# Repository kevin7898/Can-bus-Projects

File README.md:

# CAN bus projects

Experiments and applications built around CAN/OBD vehicle data.

## Projects

### [Jetta Recorder Android](jetta-recorder-android/)

An Android-first, local-first driving recorder for the Volkswagen Jetta, initially targeting a OnePlus 6T and OBDLink MX+.

The first hardware milestone establishes a real ELM327/STN connection, records standard OBD-II telemetry, captures raw CAN observations, and exports evidence for decoder development.

> Privacy: raw captures, GPS traces, VINs, and personal vehicle logs are intentionally excluded from this public repository.

### [CAN / CONNECT iOS companion](can-connect-ios/)

Native SwiftUI iPhone companion using the locked paged CAN / CONNECT design. Open `can-connect-ios/CANConnect.xcodeproj` in Xcode for vehicle onboarding, GPS and Wi-Fi ELM327 recording, fuel logging, import/export and verified transfers to the native Mac server. Hardware acceptance remains outstanding; see the iOS hardware checklist.

### [CAN / CONNECT Mac — locked design](mac-app/design/)

Approved widescreen Mac UI baseline, interactive preview, and native macOS implementation handoff. The design is locked; hardware, import, and server behavior in the preview uses illustrative data.

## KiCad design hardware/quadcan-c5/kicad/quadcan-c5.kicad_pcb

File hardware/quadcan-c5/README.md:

# QuadCAN-C5: 4-channel CAN-FD logger

**Rev 1.1 battery prototype — engineering draft, not released for manufacture.**
See [the revision notes and verification limits](docs/BATTERY_REVISION.md). Firmware for this revision is incompatible with the rev 1.0 pin map.

A custom, from-scratch take on the MrDIY DuoCAN idea, grown into a set-and-forget vehicle logger:

* **4 independent CAN / CAN-FD channels.** The ESP32-C5 has two native CAN-FD controllers, plus 2 × MCP2518FD.
* **One harness connector, swappable vehicle cables:** OBD-II (gateway + power) or heavy-duty
  **J1939** Deutsch 9-pin. Cable-ID pins tell the firmware which cable is attached. See [docs/CABLES.md](docs/CABLES.md).
* **Onboard microSD logging** with a protected 1S Li-ion backup power path and a 30-second crank grace period.
  A **real-time clock** with coin-cell backup timestamps every file.
* **Wi-Fi 6 dual-band + Wi-Fi Aware** (ESP32-C5) for a phone link, plus an optional soft-AP fallback.
* **Optional u-blox NEO-M9N GPS** at 20 Hz (25 Hz max) with an active-antenna u.FL. Leave it
  unpopulated to rely on the phone's location.
* **LTE add-on header** (UART + power key + VIN) for a Cat-1 module board.
* **9–36 V input** for 12 V cars and 24 V trucks.
* **Key-off sleep** (rev 1.1 current not yet measured): wakes on traffic on any of the four buses, an ignition wire, or the
  battery voltage rising when the engine starts. See [docs/LOW_POWER.md](docs/LOW_POWER.md).
* **Bus-safe by construction:** transceivers boot in standby, firmware opens channels listen-only,
  and a channel can't transmit at all unless its **TX_EN** jumper is fitted.

The 140 × 85 mm, four-layer prototype retains four high-speed CAN channels. It does **not** support the Jetta's 100 kbit/s fault-tolerant comfort bus without a different physical-layer design.

```mermaid
flowchart TD
    V["Protected vehicle buck"] --> O["Diode-isolated charger input"]
    U["5 V bench supply via JP9"] --> O
    O --> C["BQ24074 power path"]
    B["Protected 1S pack + NTC"] <--> C
    C --> R["5 V boost with hardware UVLO"]
    R --> T["CAN transceivers"]
    R --> L["3.3 V LDO: processor, SD, GPS"]
```

The LTE header's VIN feed is not battery-backed. JP9 defaults open; USB data remains available. A battery pack and its mounting are external to the PCB BOM.

## Repository layout

| Path | What |
|---|---|
| `gen/design.py` | **Single source of truth**: every part, footprint, MPN and pin-to-net connection |
| `gen/gen_lib.py` | Custom symbols + the ESP32-C5-WROOM-1 footprint (from Espressif's land pattern) |
| `gen/gen_sch.py` | Generates the KiCad schematic from `design.py` |
| `gen/gen_pcb.py` | Board outline, 4-layer stack, placement, ground pours |
| `gen/route.py`, `route_core.c` | Autorouter: direction-aware A* (C core) + rip-up-and-reroute; 45° tracks, In1.Cu kept as solid GND |
| `render/` | Bare-board and 3D renders (`render/render.sh` → `docs/renders/`) |
| `gen/build.sh` | Runs the whole chain: schematic → netlist check → board → route → DRC → fab files |
| `kicad/` | Generated KiCad 9 project (open `quadcan-c5.kicad_pro`) |
| `fab/` | Gerbers (zip), drill, BOM, pick-and-place, schematic PDF, DRC report |
| `firmware/` | ESP-IDF v6 firmware + `.qcl` log converter |
| `enclosure/` | OpenSCAD two-part case + STLs |
| `docs/CABLES.md` | Harness pinout, OBD-II and J1939 cable builds, jumper rules |

## Key design decisions

| Choice | Why |
|---|---|
| ESP32-C5-WROOM-1-N8R8 | Two native CAN-FD controllers, 5 GHz Wi-Fi 6, Wi-Fi Aware support in ESP-IDF, 8 MB PSRAM for a deep log buffer |
| MCP2518FD for CAN3/4 | CAN-FD, 2 KB message RAM (20-frame RX FIFO with hardware timestamps), shares SPI with the SD card |
| TCAN1044AV-Q1 | CAN-FD rated, separate 3.3 V I/O supply, ~15 µA standby with bus wake-up. NXP TJA1044GT/3 is a drop-in alternative. |
| TPS54360 60 V buck | Wide-input converter behind TVS/fuse protection; vehicle transient tolerance requires testing. |
| BQ24074 + protected 1S pack + 5 V boost | Backs the CAN and logic rails through cranking; 30-second firmware grace |
| TCA9535 expander | Frees ESP32 pins; resets to inputs, so every transceiver's STB line floats high (standby) until firmware decides otherwise |
| Molex Micro-Fit 2×7 | Locking, vibration-rated, cheap to crimp; one plug for any vehicle cable |

## Prototype status

The design is not released for ordering. See [fab/STATUS.md](fab/STATUS.md) for measured automated-check results and [docs/BATTERY_REVISION.md](docs/BATTERY_REVISION.md) for unresolved hardware and firmware gates. Fabrication data, if generated, is for engineering review only. BOM passive MPNs, pack selection and assembly rotations still need procurement review.

## Rebuilding

```sh
sudo apt install kicad   # KiCad 9.x
pip install kiutils numpy scipy pillow   # plus gcc for the router core
SKIP_ROUTE=1 bash hardware/quadcan-c5/gen/build.sh
```

The checked route cache is tied to a SHA-256 of the placement geometry. A geometry change invalidates it; omit `SKIP_ROUTE` for a new routing run, then review its new DRC results. The fine-grid finishing pass operates only on signal/ground escapes.

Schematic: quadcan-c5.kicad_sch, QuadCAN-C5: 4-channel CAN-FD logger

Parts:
BT1: CR1220; BatteryHolder_Keystone_3000_1x12mm; MPN Keystone 3000 + CR1220
C1: 47uF 63V; CP_Radial_D8.0mm_P3.50mm; MPN 47uF 63V low-ESR electrolytic, 8mm
C2, C3: 2.2uF 100V; C_1210_3225Metric; MPN 2.2uF 100V 1210 X7R/X5R
C4, C12, C14, C22, C23, C24, C25, C26, C27, C28, C29, C33, C34, C40, C42, C43, C44, C46, C47, C96, C98, C99, C100, C101, C102, C103: 100nF; C_0603_1608Metric; MPN 100nF 0603 X7R/X5R
C5, C6: 47uF 10V; C_1210_3225Metric; MPN 47uF 10V 1210 X7R/X5R
C7: 6.8nF; C_0603_1608Metric; MPN 6.8nF 0603 X7R/X5R
C8: 39pF; C_0603_1608Metric; MPN 39pF 0603 C0G
C10, C45: 10uF; C_0805_2012Metric; MPN 10uF 0805 X7R/X5R
C11, C13: 22uF; C_0805_2012Metric; MPN 22uF 0805 X7R/X5R
C15: 1uF; C_0603_1608Metric; MPN 1uF 0603 X7R/X5R
C41: 4.7uF; C_0805_2012Metric; MPN 4.7uF 0805 X7R/X5R
C90: 4.7uF 10V; C_0805_2012Metric; MPN 4.7uF 10V 0805 X7R/X5R
C91, C93: 10uF 10V; C_0805_2012Metric; MPN 10uF 10V 0805 X7R/X5R
C92, C94, C95: 22uF 10V; C_1210_3225Metric; MPN 22uF 10V 1210 X7R/X5R
C97: 1nF; C_0603_1608Metric; MPN 1nF 0603 X7R/X5R
D1: SMBJ36A; D_SMB; MPN SMBJ36A 600W TVS (36V standoff)
D2, D3: B360A; D_SMA; MPN Diodes B360A-13-F 60V 3A
D4, D5: B5819W; D_SOD-123; MPN B5819W 40V 1A
D11, D12, D13, D14: NUP2105L; SOT-23; MPN onsemi NUP2105LT1G
D21, D22, D23, D24: RX yellow; LED_0603_1608Metric; MPN 0603 LED RX yellow
D30: green; LED_0603_1608Metric; MPN 0603 LED green
D31, D32: blue; LED_0603_1608Metric; MPN 0603 LED blue
D33: GPS green; LED_0603_1608Metric; MPN 0603 LED GPS green
D40, D41: BAT54A; SOT-23; MPN BAT54A dual Schottky, common anode
F1: 2A; Fuse_Littelfuse-NANO2-451_453; MPN Littelfuse 0453002.MR (Nano2 2A 125V)
F2: 1.5A; Fuse_Littelfuse-NANO2-451_453; MPN Littelfuse 045301.5MR
H1, H2, H3, H4: M3; MountingHole_3.2mm_M3
J1: HARNESS; Molex_Micro-Fit_3.0_43045-1400_2x07_P3.00mm_Horizontal; MPN Molex 43045-1400 (mates 43025-1400 + 43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
J2: USB-C; USB_C_Receptacle_HRO_TYPE-C-31-M-12; MPN HRO TYPE-C-31-M-12
J3: microSD; microSD_HC_Hirose_DM3AT-SF-PEJM5; MPN Hirose DM3AT-SF-PEJM5
J4: GPS ANT; U.FL_Hirose_U.FL-R-SMT-1_Vertical; MPN Hirose U.FL-R-SMT-1(10) - active antenna
J5: LTE; PinHeader_1x08_P2.54mm_Vertical; MPN 1x8 2.54mm header
J6: QWIIC; JST_SH_SM04B-SRSS-TB_1x04-1MP_P1.00mm_Horizontal; MPN JST SM04B-SRSS-TB
J7: BATTERY; JST_PH_B3B-PH-K_1x03_P2.00mm_Vertical; MPN JST B3B-PH-K-S
JP1: TERM1; PinHeader_1x02_P2.54mm_Vertical; MPN 1x2 2.54mm header + jumper cap
JP2: TERM2; PinHeader_1x02_P2.54mm_Vertical; MPN 1x2 2.54mm header + jumper cap
JP3: TERM3; PinHeader_1x02_P2.54mm_Vertical; MPN 1x2 2.54mm header + jumper cap
JP4: TERM4; PinHeader_1x02_P2.54mm_Vertical; MPN 1x2 2.54mm header + jumper cap
JP5: TX_EN1; PinHeader_1x02_P2.54mm_Vertical; MPN 1x2 2.54mm header + jumper cap
JP6: TX_EN2; PinHeader_1x02_P2.54mm_Vertical; MPN 1x2 2.54mm header + jumper cap
JP7: TX_EN3; PinHeader_1x02_P2.54mm_Vertical; MPN 1x2 2.54mm header + jumper cap
JP8: TX_EN4; PinHeader_1x02_P2.54mm_Vertical; MPN 1x2 2.54mm header + jumper cap
JP9: USB_POWER; PinHeader_1x02_P2.54mm_Vertical; MPN 2.54mm jumper, default OPEN
L1: 8.2uH; L_Bourns_SRP7028A_7.3x6.6mm; MPN Bourns SRP7028A-8R2M
L2: 27nH; L_0603_1608Metric; MPN Murata LQW18AN27NG00 (27nH)
L3: 1uH; L_Bourns_SRP7028A_7.3x6.6mm; MPN Bourns SRP7028A-1R0M
Q1: MMBT3904; SOT-23; MPN MMBT3904
Q2, Q3: AO3401A; SOT-23; MPN AOS AO3401A P-MOSFET
R1: 523k; R_0603_1608Metric; MPN 523k 0603 1%
R2: 84.5k; R_0603_1608Metric; MPN 84.5k 0603 1%
R3: 162k; R_0603_1608Metric; MPN 162k 0603 1%
R4: 13.0k; R_0603_1608Metric; MPN 13.0k 0603 1%
R5: 53.6k; R_0603_1608Metric; MPN 53.6k 0603 1%
R6: 10.2k; R_0603_1608Metric; MPN 10.2k 0603 1%
R8, R14, R16, R63, R96, R99: 1M; R_0603_1608Metric; MPN 1M 0603 1%
R9, R10, R12, R64, R65, R66, R67, R73, R80, R92, R93, R95, R100, R102: 100k; R_0603_1608Metric; MPN 100k 0603 1%
R11, R17, R20, R21, R22, R53, R55, R60, R61, R62, R104, R105: 10k; R_0603_1608Metric; MPN 10k 0603 1%
R13, R15, R41, R42, R43, R44, R70, R71, R72, R81, R82, R84: 1k; R_0603_1608Metric; MPN 1k 0603 1%
R18, R19: 4.7k; R_0603_1608Metric; MPN 4.7k 0603 1%
R23, R24: 5.1k; R_0603_1608Metric; MPN 5.1k 0603 1%
R31, R32, R33, R34: 120R; R_1206_3216Metric; MPN 120R 1206 1%
R83: 22R; R_1206_3216Metric; MPN 22R 1206 1%
R90: 8.87k; R_0603_1608Metric; MPN 8.87k 0603 1%
R91: 1.62k; R_0603_1608Metric; MPN 1.62k 0603 1%
R94: 732k; R_0603_1608Metric; MPN 732k 0603 1%
R97: 560k; R_0603_1608Metric; MPN 560k 0603 1%
R98: 6.34M; R_0603_1608Metric; MPN 6.34M 0603 1%
R101, R103: 33k; R_0603_1608Metric; MPN 33k 0603 1%
SW1: RESET; SW_SPST_PTS810; MPN C&K PTS810 SJM 250 SMTR LFS
SW2: BOOT; SW_SPST_PTS810; MPN C&K PTS810 SJM 250 SMTR LFS
SW3: MARK; SW_SPST_PTS810; MPN C&K PTS810 SJM 250 SMTR LFS
U1: TPS54360DDA; TI_SO-PowerPAD-8_ThermalVias; MPN TI TPS54360DDAR (60V 3.5A buck)
U2: AP7361C-33E; SOT-223-3_TabPin2; MPN Diodes AP7361C-33E-13 (1A LDO)
U3: ESP32-C5-WROOM-1-N8R8; ESP32-C5-WROOM-1; MPN Espressif ESP32-C5-WROOM-1-N8R8 (8MB fl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
U4: USBLC6-2SC6; SOT-23-6; MPN ST USBLC6-2SC6
U5, U6, U7, U8: TCAN1044AV-Q1; SOIC-8_3.9x4.9mm_P1.27mm; MPN TI TCAN1044AVDRQ1 (alt: NXP TJA1044GT/3)
U9, U10: MCP2518FD; SOIC-14_3.9x8.7mm_P1.27mm; MPN Microchip MCP2518FDT-E/SL
U11: TCA9535PWR; TSSOP-24_4.4x7.8mm_P0.65mm; MPN TI TCA9535PWR (I2C 0x20)
U12: PCF8523T; SOIC-8_3.9x4.9mm_P1.27mm; MPN NXP PCF8523T/1 (I2C 0x68)
U13: NEO-M9N; ublox_NEO; MPN u-blox NEO-M9N-00B (25 Hz)
U14: BQ24074; BQ24074_ThermalVia03; MPN TI BQ24074RGTR
U15: TPS61023; SOT-563; MPN TI TPS61023DRLR
U16: TLV3012B; SOT-23-6; MPN TI TLV3012BIDBVR
U17: TCA9535 0x21; TSSOP-24_4.4x7.8mm_P0.65mm; MPN TI TCA9535PWR
U18: ADS1115 0x48; TSSOP-10_3x3mm_P0.5mm; MPN TI ADS1115IDGSR
U19: 74LVC1G08; SOT-23-5; MPN TI SN74LVC1G08DBVR
U20: 74LVC1G125; SOT-23-5; MPN TI SN74LVC1G125DBVR
Y1: 40MHz; Oscillator_SMD_Abracon_ASE-4Pin_3.2x2.5mm; MPN Abracon ASE-40.000MHZ-LC-T (3.3V CMOS)
Y2: 32.768kHz; Crystal_SMD_3215-2Pin_3.2x1.5mm; MPN Abracon ABS07-32.768KHZ-7-T (7pF)

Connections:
+3V3: C11.1, C13.1, C14.1, C23.1, C25.1, C27.1, C29.1, C33.1, C34.1, C40.1, C43.1, C44.1, C98.1, C99.1, C102.1, C103.1, J5.3, J6.2, Q2.2 (S), Q3.2 (S), R12.1, R14.1, R16.1, R17.1, R18.1, R19.1, R21.1, R22.1, R41.1, R42.1, R43.1, R44.1, R53.1, R55.1, R63.1, R64.1, R67.1, R70.1, R71.1, R72.1, R73.1, R80.1, R92.1, R93.1, R104.1, R105.1, U2.3 (VO), U3.2 (3V3), U5.5 (VIO), U6.5 (VIO), U7.5 (VIO), U8.5 (VIO), U9.14 (VDD), U10.14 (VDD), U11.24 (VCC), U12.8 (VDD), U13.22 (V_BCKP), U17.21 (A0), U17.24 (VCC), U18.8 (VDD), U19.5 (VCC), U20.5 (VCC), Y1.4 (Vdd)
+5V: C10.1, C22.1, C24.1, C26.1, C28.1, C94.1, C95.1, R94.1, U2.1 (VI), U5.3 (VCC), U6.3 (VCC), U7.3 (VCC), U8.3 (VCC), U15.6 (VOUT)
BAT: C91.1, F2.2, R100.1, U14.2 (BAT), U14.3 (BAT)
BAT_ADC: C100.1, R100.2, R101.1, U18.4 (AIN0)
BAT_PACK: F2.1, J7.1
BAT_TS: J7.2, U14.1 (TS)
BOOST_EN: R98.1, R99.1, U15.2 (EN), U16.1 (OUT)
BOOST_FB: R94.2, R95.1, U15.1 (FB)
BOOST_SW: L3.2, U15.5 (SW)
BTN_MARK_N: R73.2, SW3.1, U11.19 (P16)
BUCK_BOOT: C4.1, U1.1 (BOOT)
BUCK_COMP: C8.1, R4.1, U1.6 (COMP)
BUCK_CZ: C7.1, R4.2
BUCK_EN: R1.2, R2.1, U1.3 (EN)
BUCK_FB: R5.2, R6.1, U1.5 (FB)
BUCK_RT: R3.1, U1.4 (RT/CLK)
BUCK_SW: C4.2, D3.1 (K), L1.1, U1.8 (SW)
CABLE_ID0: R13.2, R14.2, U11.14 (P11)
CABLE_ID0_RAW: J1.7, R13.1
CABLE_ID1: R15.2, R16.2, U11.15 (P12)
CABLE_ID1_RAW: J1.14, R15.1
CAN1_H: D11.1 (K), J1.3, R31.1, U5.7 (CANH)
CAN1_L: D11.2 (K), J1.10, JP1.2, U5.6 (CANL)
CAN1_RXD: D21.1 (K), U3.5 (IO3), U5.4 (RXD)
CAN1_STB: U5.8 (STB), U11.4 (P00)
CAN1_TERM: JP1.1, R31.2
CAN1_TXD: JP5.2, U5.1 (TXD)
CAN1_TXD_MCU: JP5.1, U3.6 (IO0)
CAN2_H: D12.1 (K), J1.4, R32.1, U6.7 (CANH)
CAN2_L: D12.2 (K), J1.11, JP2.2, U6.6 (CANL)
CAN2_RXD: D22.1 (K), U3.7 (IO1), U6.4 (RXD)
CAN2_STB: U6.8 (STB), U11.5 (P01)
CAN2_TERM: JP2.1, R32.2
CAN2_TXD: JP6.2, U6.1 (TXD)
CAN2_TXD_MCU: JP6.1, U3.10 (IO8)
CAN3_CS: R21.2, U3.11 (IO9), U9.13 (~CS)
CAN3_H: D13.1 (K), J1.5, R33.1, U7.7 (CANH)
CAN3_INT_N: R53.2, U9.4 (~INT), U19.1
CAN3_L: D13.2 (K), J1.12, JP3.2, U7.6 (CANL)
CAN3_RXD: D23.1 (K), D40.1, U7.4 (RXD), U9.2 (RXCAN)
CAN3_STB: U7.8 (STB), U9.9 (~INT0/GPIO0/XSTBY)
CAN3_TERM: JP3.1, R33.2
CAN3_TXD: JP7.2, U7.1 (TXD)
CAN3_TXD_MCU: JP7.1, U9.1 (TXCAN)
CAN4_CS: R22.2, U3.12 (IO10), U10.13 (~CS)
CAN4_H: D14.1 (K), J1.6, R34.1, U8.7 (CANH)
CAN4_INT_N: R104.2, U10.4 (~INT), U19.2
CAN4_L: D14.2 (K), J1.13, JP4.2, U8.6 (CANL)
CAN4_RXD: D24.1 (K), D40.2, U8.4 (RXD), U10.2 (RXCAN)
CAN4_STB: U8.8 (STB), U10.9 (~INT0/GPIO0/XSTBY)
CAN4_TERM: JP4.1, R34.2
CAN4_TXD: JP8.2, U8.1 (TXD)
CAN4_TXD_MCU: JP8.1, U10.1 (TXCAN)
CAN34_INT: U3.21 (IO23), U19.4
CHG_ILIM: R91.1, U14.12 (ILIM)
CHG_IN: C90.1, D4.1 (K), D5.1 (K), U14.5 (EN2), U14.13 (IN)
CHG_ISET: R90.1, U14.16 (ISET)
CHG_N: R93.2, U14.9 (CHG_N), U17.5 (P01)
CLK40: U9.6 (OSC1), U10.6 (OSC1), Y1.3 (OUT)
EN: C15.1, R17.2, SW1.1, U3.3 (EN)
ESP_GPS_RX: R82.2, U3.27 (IO26)
ESP_LTE_RX: J5.5, U3.24 (RX0/IO12)
ESP_LTE_TX: J5.4, U3.25 (TX0/IO11)
GND: BT1.2 (-), C1.2, C2.2, C3.2, C5.2, C6.2, C7.2, C8.2, C10.2, C11.2, C12.2, C13.2, C14.2, C15.2, C22.2, C23.2, C24.2, C25.2, C26.2, C27.2, C28.2, C29.2, C33.2, C34.2, C40.2, C41.2, C42.2, C43.2, C44.2, C45.2, C46.2, C47.2, C90.2, C91.2, C92.2, C93.2, C94.2, C95.2, C96.2, C97.2, C98.2, C99.2, C100.2, C101.2, C102.2, C103.2, D1.2 (A), D3.2 (A), D11.3 (A), D12.3 (A), D13.3 (A), D14.3 (A), D33.1 (K), J1.2, J1.8, J2.A1 (GND), J2.A12 (GND), J2.B1 (GND), J2.B12 (GND), J2.S1 (SHIELD), J3.6 (VSS), J3.9 (DET_B), J3.11 (SHIELD), J4.2 (Ext), J5.2, J5.8, J6.1, J6.MP (MountPin), J7.3, Q1.2 (E), R2.2, R3.2, R6.2, R9.2, R11.2, R23.2, R24.2, R65.2, R66.2, R90.2, R91.2, R95.2, R97.2, R99.2, R101.2, R103.2, SW1.2, SW2.2, SW3.2, U1.7 (GND), U1.9 (GNDPAD), U2.2 (GND), U3.1 (GND), U3.28 (GND), U3.29 (EPAD_GND), U4.2 (GND), U5.2 (GND), U6.2 (GND), U7.2 (GND), U8.2 (GND), U9.7 (VSS), U10.7 (VSS), U11.2 (A1), U11.3 (A2), U11.12 (GND), U11.21 (A0), U12.4 (VSS), U13.7 (VDD_USB), U13.10 (GND), U13.12 (GND), U13.13 (GND), U13.24 (GND), U14.4 (CE_N), U14.6 (EN1), U14.8 (GND), U14.17 (EP), U15.4 (GND), U16.2 (V-), U17.2 (A1), U17.3 (A2), U17.6 (P02), U17.7 (P03), U17.8 (P04), U17.9 (P05), U17.10 (P06), U17.11 (P07), U17.12 (GND), U17.13 (P10), U17.14 (P11), U17.15 (P12), U17.16 (P13), U17.17 (P14), U17.18 (P15), U17.19 (P16), U17.20 (P17), U18.1 (ADDR), U18.3 (GND), U18.6 (AIN2), U18.7 (AIN3), U19.3 (GND), U20.3 (GND), Y1.2 (GND)
GPS_3V3: C45.1, C46.1, Q2.3 (D), U13.23 (VCC)
GPS_BIAS: C47.1, L2.1, R83.2
GPS_PPS: R84.1, U13.3 (TIMEPULSE)
GPS_PWR_N: Q2.1 (G), R80.2, U11.10 (P06), U20.1
GPS_RESET_N: U11.17 (P14), U13.8 (~RESET)
GPS_RF: J4.1 (In), L2.2, U13.11 (RF_IN)
GPS_RXD: R81.2, U13.21 (RXD/SPI_MOSI)
GPS_TXD: R82.1, U13.20 (TXD/SPI_MISO)
GPS_TX_BUFFERED: R81.1, U20.4
GPS_TX_STRAP: R105.2, U3.18 (IO27), U20.2
GPS_VCC_RF: R83.1, U13.9 (VCC_RF)
I2C_SCL: J6.4, R19.2, SW2.1, U3.15 (IO28), U11.22 (SCL), U12.6 (SCL), U17.22 (SCL), U18.10 (SCL)
I2C_SDA: J6.3, R18.2, U3.26 (IO25), U11.23 (SDA), U12.5 (SDA), U17.23 (SDA), U18.9 (SDA)
IGN_B: Q1.1 (B), R10.2, R11.1
IGN_N: D41.1, D41.2, Q1.3 (C), R12.2, U11.13 (P10)
IGN_RAW: J1.9, R10.1
LED_GPS_A: D33.2 (A), R84.2
LED_LINK_A: D32.2 (A), R72.2
LED_LINK_N: D32.1 (K), U11.8 (P04)
LED_RX1_A: D21.2 (A), R41.2
LED_RX2_A: D22.2 (A), R42.2
LED_RX3_A: D23.2 (A), R43.2
LED_RX4_A: D24.2 (A), R44.2
LED_SD_A: D31.2 (A), R71.2
LED_SD_N: D31.1 (K), U11.7 (P03)
LED_STAT_A: D30.2 (A), R70.2
LED_STAT_N: D30.1 (K), U11.6 (P02)
LTE_PWRKEY: J5.6, U11.11 (P07)
LTE_STATUS: J5.7, U11.18 (P15)
OSC_EN: R55.2, U11.9 (P05), Y1.1 (EN)
PGOOD_N: R92.2, U14.7 (PGOOD_N), U17.4 (P00)
RTC_XI: U12.1 (OSCI), Y2.1
RTC_XO: U12.2 (OSCO), Y2.2
SD_3V3: C41.1, C42.1, J3.4 (VDD), Q3.3 (D), R20.1, R60.1, R61.1, R62.1
SD_CS: J3.2 (DAT3/CD), R20.2, U3.23 (IO24)
SD_DAT1: J3.8 (DAT1), R60.2
SD_DAT2: J3.1 (DAT2), R61.2
SD_DET: J3.10 (DET_A), R63.2, U11.16 (P13)
SD_PWR_N: Q3.1 (G), R64.2, U11.20 (P17)
SPI_MISO: J3.7 (DAT0), R62.2, U3.4 (IO2), U9.12 (SDO), U10.12 (SDO)
SPI_MOSI: J3.3 (CMD), R66.1, U3.9 (IO7), U9.11 (SDI), U10.11 (SDI)
SPI_SCK: J3.5 (CLK), R65.1, U3.8 (IO6), U9.10 (SCK), U10.10 (SCK)
SYS_ADC: C101.1, R102.2, R103.1, U18.5 (AIN1)
USB_CC1: J2.A5 (CC1), R23.1
USB_CC2: J2.B5 (CC2), R24.1
USB_DN: J2.A7 (D-), J2.B7 (D-), U3.13 (IO13/USB_D-), U4.3 (I/O2), U4.4 (I/O2)
USB_DP: J2.A6 (D+), J2.B6 (D+), U3.14 (IO14/USB_D+), U4.1 (I/O1), U4.6 (I/O1)
USB_PWR: D4.2 (A), JP9.2
UVLO_REF: C97.1, U16.4 (IN-), U16.5 (REF)
UVLO_SENSE: R96.2, R97.1, R98.2, U16.3 (IN+)
VBAT_RTC: BT1.1 (+), U12.3 (VBAT)
VBUS: J2.A4 (VBUS), J2.A9 (VBUS), J2.B4 (VBUS), J2.B9 (VBUS), JP9.1, U4.5 (VBUS)
VEH_5V: C5.1, C6.1, D5.2 (A), L1.2, R5.1
VIN: C1.1, C2.1, C3.1, D2.1 (K), J5.1, R1.1, R8.1, U1.2 (VIN)
VIN_F: D1.1 (K), D2.2 (A), F1.2
VIN_RAW: F1.1, J1.1
VIN_SENSE: C12.1, R8.2, R9.1, U3.17 (IO4)
VSYS: C92.1, C93.1, C96.1, L3.1, R96.1, R102.1, U14.10 (OUT), U14.11 (OUT), U15.3 (VIN), U16.6 (V+)
WAKE_N: D40.3, D41.3, R67.2, U3.16 (IO5)

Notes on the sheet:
VEHICLE INPUT: protected 9-36V -> 5V buck; battery-backed rails below
J1: Harness: 1 VIN, 2/8 GND, 3-6 CAN1-4 H, 10-13 CAN1-4 L, 9 IGN, 7/14 cable ID
D1: TVS: load dump / jump start; reverse polarity blows F1 via D1
D2: Reverse polarity block
U1: Values from TI TPS54360 datasheet 5V design example (Fig. 34)
R2: UVLO: start 8V, stop 6.25V
R3: fsw ~600 kHz
D3: Catch diode
D4: USB bench supply only through JP9; use a rated 5V source, not an unnegotiated host port
D5: Vehicle/USB input OR; battery cannot backfeed either input
VIN / IGNITION / CABLE-ID SENSE
R9: VIN/11 -> ADC; 36V = 3.27V
Q1: IGN > ~6.5V pulls IGN_N low (6-60V safe)
D40: WAKE_N goes low on CAN3/CAN4 bus activity (transceiver in standby) or ignition on
R67: Deep-sleep wake sources: GPIO3 CAN1_RXD, GPIO1 CAN2_RXD, GPIO5 WAKE_N
R16: Cable grounds ID0/ID1 to identify itself (1M: 3 uA in sleep)
MCU: ESP32-C5-WROOM-1 (2x native CAN-FD, Wi-Fi 6 + Wi-Fi Aware)
U3: GPIO23 MCP IRQ; GPIO26 GPS RX; GPIO27 GPS TX via disabled-at-reset buffer
SW2: Hold BOOT while tapping RESET for download mode
USB-C (native USB Serial/JTAG)
J2: Native USB Serial/JTAG: flashing, console, config
CAN1 (native CAN-FD 0) - OBD gateway pins 6/14
U5: STB has internal pull-up: transceiver boots in standby
JP1: Fit ONLY when the logger is a bus end
JP5: TX ENABLE: no jumper = channel physically cannot transmit
CAN2 (native CAN-FD 1)
U6: STB has internal pull-up: transceiver boots in standby
CAN3 (MCP2518FD #1) + shared 40MHz clock
U7: STB has internal pull-up: transceiver boots in standby
U9: INT isolated by AND gate; byte-write IOCON; STB through XSTBY
Y1: One clock for both MCP2518FD; expander can stop it in sleep
U19: Active-low interrupts combined without tying outputs together
CAN4 (MCP2518FD #2)
U8: STB has internal pull-up: transceiver boots in standby
U10: INT isolated by AND gate; byte-write IOCON; STB through XSTBY
microSD (SPI)
J3: SPI mode, shares the bus with the MCP2518FDs
Q3: SD card power switch: card is unpowered in sleep (idle cards can draw ~1 mA)
R65: Keep the SPI bus defined while the MCU sleeps
IO EXPANDER, STATUS LEDS, MARK BUTTON

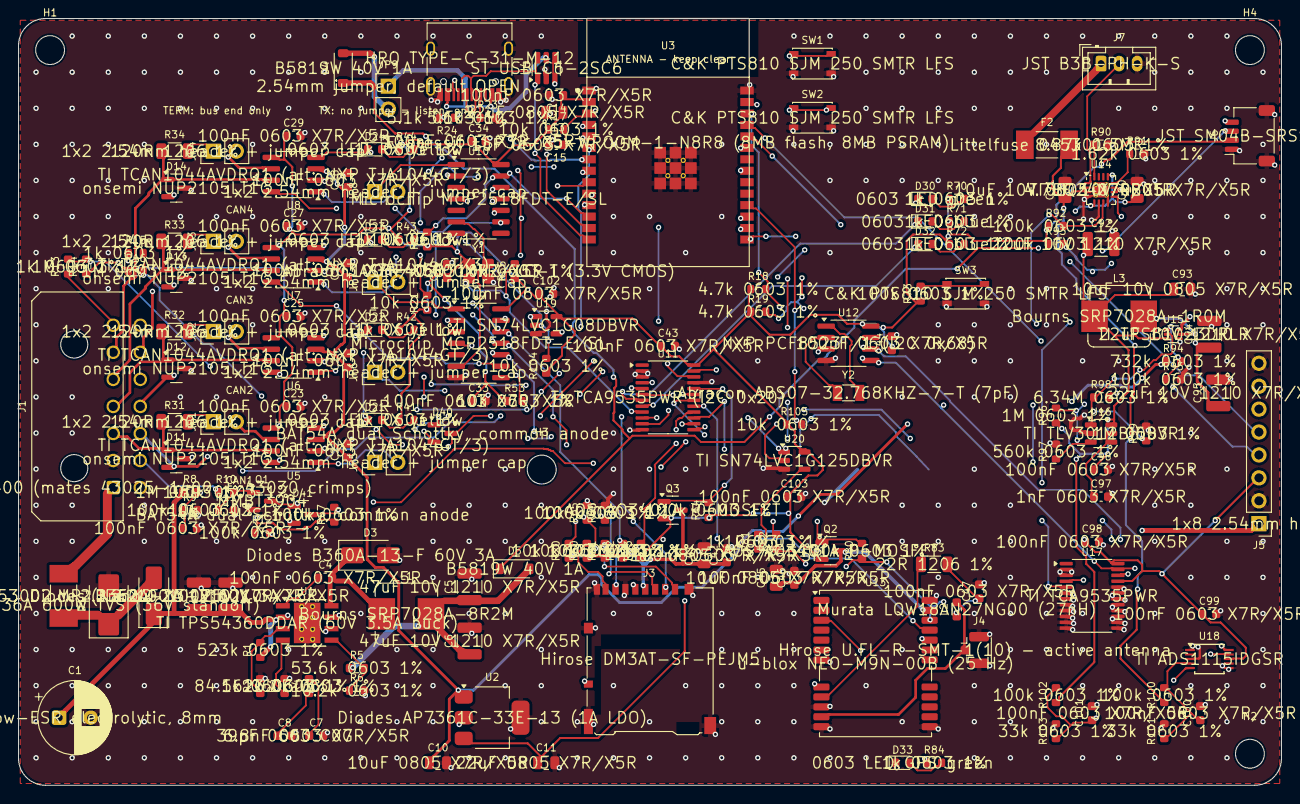
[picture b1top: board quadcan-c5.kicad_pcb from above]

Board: 4 copper layers, 140.0 x 85.0 mm, 185 parts (1 on the bottom side), 123 nets.

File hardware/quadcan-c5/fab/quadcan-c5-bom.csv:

Qty,Designator,Value,Footprint,Manufacturer part / notes,Assembly
1,BT1,CR1220,BatteryHolder_Keystone_3000_1x12mm,Keystone 3000 + CR1220,hand-solder (THT)
1,C1,47uF 63V,CP_Radial_D8.0mm_P3.50mm,"47uF 63V low-ESR electrolytic, 8mm",hand-solder (THT)
2,C10 C45,10uF,C_0805_2012Metric,10uF 0805 X7R/X5R,SMT
2,C11 C13,22uF,C_0805_2012Metric,22uF 0805 X7R/X5R,SMT
1,C15,1uF,C_0603_1608Metric,1uF 0603 X7R/X5R,SMT
2,C2 C3,2.2uF 100V,C_1210_3225Metric,2.2uF 100V 1210 X7R/X5R,SMT
26,C100 C101 C102 C103 C12 C14 C22 C23 C24 C25 C26 C27 C28 C29 C33 C34 C4 C40 C42 C43 C44 C46 C47 C96 C98 C99,100nF,C_0603_1608Metric,100nF 0603 X7R/X5R,SMT
1,C41,4.7uF,C_0805_2012Metric,4.7uF 0805 X7R/X5R,SMT
2,C5 C6,47uF 10V,C_1210_3225Metric,47uF 10V 1210 X7R/X5R,SMT
1,C7,6.8nF,C_0603_1608Metric,6.8nF 0603 X7R/X5R,SMT
1,C8,39pF,C_0603_1608Metric,39pF 0603 C0G,SMT
1,C90,4.7uF 10V,C_0805_2012Metric,4.7uF 10V 0805 X7R/X5R,SMT
2,C91 C93,10uF 10V,C_0805_2012Metric,10uF 10V 0805 X7R/X5R,SMT
3,C92 C94 C95,22uF 10V,C_1210_3225Metric,22uF 10V 1210 X7R/X5R,SMT
1,C97,1nF,C_0603_1608Metric,1nF 0603 X7R/X5R,SMT
1,D1,SMBJ36A,D_SMB,SMBJ36A 600W TVS (36V standoff),SMT
4,D11 D12 D13 D14,NUP2105L,SOT-23,onsemi NUP2105LT1G,SMT
2,D2 D3,B360A,D_SMA,Diodes B360A-13-F 60V 3A,SMT
4,D21 D22 D23 D24,RX yellow,LED_0603_1608Metric,0603 LED RX yellow,SMT
1,D30,green,LED_0603_1608Metric,0603 LED green,SMT
2,D31 D32,blue,LED_0603_1608Metric,0603 LED blue,SMT
1,D33,GPS green,LED_0603_1608Metric,0603 LED GPS green,SMT
2,D4 D5,B5819W,D_SOD-123,B5819W 40V 1A,SMT
2,D40 D41,BAT54A,SOT-23,"BAT54A dual Schottky, common anode",SMT
1,F1,2A,Fuse_Littelfuse-NANO2-451_453,Littelfuse 0453002.MR (Nano2 2A 125V),SMT
1,F2,1.5A,Fuse_Littelfuse-NANO2-451_453,Littelfuse 045301.5MR,SMT
1,J1,HARNESS,Molex_Micro-Fit_3.0_43045-1400_2x07_P3.00mm_Horizontal,Molex 43045-1400 (mates 43025-1400 + 43030 crimps),hand-solder (THT)
1,J2,USB-C,USB_C_Receptacle_HRO_TYPE-C-31-M-12,HRO TYPE-C-31-M-12,SMT
1,J3,microSD,microSD_HC_Hirose_DM3AT-SF-PEJM5,Hirose DM3AT-SF-PEJM5,SMT
1,J4,GPS ANT,U.FL_Hirose_U.FL-R-SMT-1_Vertical,Hirose U.FL-R-SMT-1(10) - active antenna,SMT
1,J5,LTE,PinHeader_1x08_P2.54mm_Vertical,1x8 2.54mm header,hand-solder (THT)
1,J6,QWIIC,JST_SH_SM04B-SRSS-TB_1x04-1MP_P1.00mm_Horizontal,JST SM04B-SRSS-TB,SMT
1,J7,BATTERY,JST_PH_B3B-PH-K_1x03_P2.00mm_Vertical,JST B3B-PH-K-S,hand-solder (THT)
1,JP1,TERM1,PinHeader_1x02_P2.54mm_Vertical,1x2 2.54mm header + jumper cap,hand-solder (THT)
1,JP2,TERM2,PinHeader_1x02_P2.54mm_Vertical,1x2 2.54mm header + jumper cap,hand-solder (THT)
1,JP3,TERM3,PinHeader_1x02_P2.54mm_Vertical,1x2 2.54mm header + jumper cap,hand-solder (THT)
1,JP4,TERM4,PinHeader_1x02_P2.54mm_Vertical,1x2 2.54mm header + jumper cap,hand-solder (THT)
1,JP5,TX_EN1,PinHeader_1x02_P2.54mm_Vertical,1x2 2.54mm header + jumper cap,hand-solder (THT)
1,JP6,TX_EN2,PinHeader_1x02_P2.54mm_Vertical,1x2 2.54mm header + jumper cap,hand-solder (THT)
1,JP7,TX_EN3,PinHeader_1x02_P2.54mm_Vertical,1x2 2.54mm header + jumper cap,hand-solder (THT)
1,JP8,TX_EN4,PinHeader_1x02_P2.54mm_Vertical,1x2 2.54mm header + jumper cap,hand-solder (THT)
1,JP9,USB_POWER,PinHeader_1x02_P2.54mm_Vertical,"2.54mm jumper, default OPEN",hand-solder (THT)
1,L1,8.2uH,L_Bourns_SRP7028A_7.3x6.6mm,Bourns SRP7028A-8R2M,SMT
1,L2,27nH,L_0603_1608Metric,Murata LQW18AN27NG00 (27nH),SMT
1,L3,1uH,L_Bourns_SRP7028A_7.3x6.6mm,Bourns SRP7028A-1R0M,SMT
1,Q1,MMBT3904,SOT-23,MMBT3904,SMT
2,Q2 Q3,AO3401A,SOT-23,AOS AO3401A P-MOSFET,SMT
1,R1,523k,R_0603_1608Metric,523k 0603 1%,SMT
2,R101 R103,33k,R_0603_1608Metric,33k 0603 1%,SMT
12,R104 R105 R11 R17 R20 R21 R22 R53 R55 R60 R61 R62,10k,R_0603_1608Metric,10k 0603 1%,SMT
12,R13 R15 R41 R42 R43 R44 R70 R71 R72 R81 R82 R84,1k,R_0603_1608Metric,1k 0603 1%,SMT
2,R18 R19,4.7k,R_0603_1608Metric,4.7k 0603 1%,SMT
1,R2,84.5k,R_0603_1608Metric,84.5k 0603 1%,SMT
2,R23 R24,5.1k,R_0603_1608Metric,5.1k 0603 1%,SMT
1,R3,162k,R_0603_1608Metric,162k 0603 1%,SMT
4,R31 R32 R33 R34,120R,R_1206_3216Metric,120R 1206 1%,SMT
1,R4,13.0k,R_0603_1608Metric,13.0k 0603 1%,SMT
1,R5,53.6k,R_0603_1608Metric,53.6k 0603 1%,SMT
1,R6,10.2k,R_0603_1608Metric,10.2k 0603 1%,SMT
6,R14 R16 R63 R8 R96 R99,1M,R_0603_1608Metric,1M 0603 1%,SMT
1,R83,22R,R_1206_3216Metric,22R 1206 1%,SMT
14,R10 R100 R102 R12 R64 R65 R66 R67 R73 R80 R9 R92 R93 R95,100k,R_0603_1608Metric,100k 0603 1%,SMT
1,R90,8.87k,R_0603_1608Metric,8.87k 0603 1%,SMT
1,R91,1.62k,R_0603_1608Metric,1.62k 0603 1%,SMT
1,R94,732k,R_0603_1608Metric,732k 0603 1%,SMT
1,R97,560k,R_0603_1608Metric,560k 0603 1%,SMT
1,R98,6.34M,R_0603_1608Metric,6.34M 0603 1%,SMT
1,SW1,RESET,SW_SPST_PTS810,C&K PTS810 SJM 250 SMTR LFS,SMT
1,SW2,BOOT,SW_SPST_PTS810,C&K PTS810 SJM 250 SMTR LFS,SMT
1,SW3,MARK,SW_SPST_PTS810,C&K PTS810 SJM 250 SMTR LFS,SMT
1,U1,TPS54360DDA,TI_SO-PowerPAD-8_ThermalVias,TI TPS54360DDAR (60V 3.5A buck),SMT
1,U11,TCA9535PWR,TSSOP-24_4.4x7.8mm_P0.65mm,TI TCA9535PWR (I2C 0x20),SMT
1,U12,PCF8523T,SOIC-8_3.9x4.9mm_P1.27mm,NXP PCF8523T/1 (I2C 0x68),SMT
1,U13,NEO-M9N,ublox_NEO,u-blox NEO-M9N-00B (25 Hz),SMT - optional GPS
1,U14,BQ24074,BQ24074_ThermalVia03,TI BQ24074RGTR,SMT
1,U15,TPS61023,SOT-563,TI TPS61023DRLR,SMT
1,U16,TLV3012B,SOT-23-6,TI TLV3012BIDBVR,SMT
1,U17,TCA9535 0x21,TSSOP-24_4.4x7.8mm_P0.65mm,TI TCA9535PWR,SMT
1,U18,ADS1115 0x48,TSSOP-10_3x3mm_P0.5mm,TI ADS1115IDGSR,SMT
1,U19,74LVC1G08,SOT-23-5,TI SN74LVC1G08DBVR,SMT
1,U2,AP7361C-33E,SOT-223-3_TabPin2,Diodes AP7361C-33E-13 (1A LDO),SMT
1,U20,74LVC1G125,SOT-23-5,TI SN74LVC1G125DBVR,SMT
1,U3,ESP32-C5-WROOM-1-N8R8,ESP32-C5-WROOM-1,"Espressif ESP32-C5-WROOM-1-N8R8 (8MB flash, 8MB PSRAM)",SMT
1,U4,USBLC6-2SC6,SOT-23-6,ST USBLC6-2SC6,SMT
4,U5 U6 U7 U8,TCAN1044AV-Q1,SOIC-8_3.9x4.9mm_P1.27mm,TI TCAN1044AVDRQ1 (alt: NXP TJA1044GT/3),SMT
2,U10 U9,MCP2518FD,SOIC-14_3.9x8.7mm_P1.27mm,Microchip MCP2518FDT-E/SL,SMT
1,Y1,40MHz,Oscillator_SMD_Abracon_ASE-4Pin_3.2x2.5mm,Abracon ASE-40.000MHZ-LC-T (3.3V CMOS),SMT
1,Y2,32.768kHz,Crystal_SMD_3215-2Pin_3.2x1.5mm,Abracon ABS07-32.768KHZ-7-T (7pF),SMT

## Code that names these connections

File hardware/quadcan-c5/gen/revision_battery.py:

"""Rev 1.1 battery power path. Pin numbers checked against manufacturer datasheets.

Design target only: protected 1S 4.2 V Li-ion pack, >=500 mAh, >=2 A discharge,
103AT-2-compatible pack-mounted 10k NTC. No LiFePO4 substitution.
"""
def revise(parts, P, R, C):
    removed = {'C9', 'D6', 'R7'}
    parts[:] = [p for p in parts if p['ref'] not in removed]
    d = {p['ref']: p for p in parts}
    # The old +5V buck output becomes VEH_5V. +5V now comes only from the boost.
    for ref in ('L1', 'C5', 'C6', 'R5'):
        d[ref]['pins'] = {k: ('VEH_5V' if v == '+5V' else v) for k,v in d[ref]['pins'].items()}
    # Diode OR keeps vehicle buck and USB isolated. USB power is optional via JP9.
    d['D4']['pins'] = {'1':'CHG_IN','2':'USB_PWR'}
    d['D5']['pins'] = {'1':'CHG_IN','2':'VEH_5V'}
    d['D4']['note'] = 'USB bench supply only through JP9; use a rated 5V source, not an unnegotiated host port'
    d['D5']['note'] = 'Vehicle/USB input OR; battery cannot backfeed either input'
    d['U2']['pins']['1'] = '+5V'
    d['C10']['pins']['1'] = '+5V'
    # Gate-combine interrupts; neither controller can fight the other at reset.
    d['U9']['pins']['4'] = 'CAN3_INT_N'
    d['U10']['pins']['4'] = 'CAN4_INT_N'
    d['R53']['pins']['2'] = 'CAN3_INT_N'
    # GPS RX moves off boot strap; boot strap becomes isolated UART output.
    d['U3']['pins'].update({'18':'GPS_TX_STRAP','21':'CAN34_INT','27':'ESP_GPS_RX'})
    d['U3']['note'] = 'GPIO23 MCP IRQ; GPIO26 GPS RX; GPIO27 GPS TX via disabled-at-reset buffer'
    d['R81']['pins']['1'] = 'GPS_TX_BUFFERED'
    for ref in ('U9','U10'):
        d[ref]['note'] = 'INT isolated by AND gate; byte-write IOCON; STB through XSTBY'
    add = parts.append
    s6='Package_TO_SOT_SMD:SOT-23-6'
    s5='Package_TO_SOT_SMD:SOT-23-5'
    c8='Capacitor_SMD:C_0805_2012Metric'
    c12='Capacitor_SMD:C_1210_3225Metric'
    add(P('JP9','Connector_Generic:Conn_01x02','Connector_PinHeader_2.54mm:PinHeader_1x02_P2.54mm_Vertical','USB_POWER','2.54mm jumper, default OPEN',{'1':'VBUS','2':'USB_PWR'},'battery','Fit only for a >=1A 5V bench supply; USB data works without jumper'))
    add(P('J7','Connector_Generic:Conn_01x03','Connector_JST:JST_PH_B3B-PH-K_1x03_P2.00mm_Vertical','BATTERY','JST B3B-PH-K-S',{'1':'BAT_PACK','2':'BAT_TS','3':'GND'},'battery','Verify pack polarity: 1 plus, 2 NTC, 3 minus; protected 1S Li-ion only'))
    add(P('F2','Device:Fuse','Fuse:Fuse_Littelfuse-NANO2-451_453','1.5A','Littelfuse 045301.5MR',{'1':'BAT_PACK','2':'BAT'},'battery'))
    add(P('U14','QuadCAN:BQ24074','QuadCAN:BQ24074_ThermalVia03','BQ24074','TI BQ24074RGTR',
          {'1':'BAT_TS','2':'BAT','3':'BAT','4':'GND','5':'CHG_IN','6':'GND','7':'PGOOD_N','8':'GND','9':'CHG_N','10':'VSYS','11':'VSYS','12':'CHG_ILIM','13':'CHG_IN','16':'CHG_ISET','17':'GND'},'battery',
          'ITERM/TMR intentionally open: default termination/timers; TS must reach actual pack NTC'))
    add(R('R90','8.87k','CHG_ISET','GND','battery',note='Nominal 100mA charge, worst KISET ~110mA'))
    add(R('R91','1.62k','CHG_ILIM','GND','battery',note='Nominal ~0.99A input limit; total board plus charging'))
    add(R('R92','100k','+3V3','PGOOD_N','battery'))
    add(R('R93','100k','+3V3','CHG_N','battery'))
    add(C('C90','4.7uF 10V','CHG_IN','GND','battery',c8))
    add(C('C91','10uF 10V','BAT','GND','battery',c8))
    add(C('C92','22uF 10V','VSYS','GND','battery',c12))
    add(P('U15','QuadCAN:TPS61023','Package_TO_SOT_SMD:SOT-563','TPS61023','TI TPS61023DRLR',
          {'1':'BOOST_FB','2':'BOOST_EN','3':'VSYS','4':'GND','5':'BOOST_SW','6':'+5V'},'battery','5V boost with true output disconnect; enables only above hardware UVLO'))
    add(P('L3','Device:L','Inductor_SMD:L_Bourns_SRP7028A_7.3x6.6mm','1uH','Bourns SRP7028A-1R0M',{'1':'VSYS','2':'BOOST_SW'},'battery','Verify saturation >= peak switch current over temperature'))
    add(R('R94','732k','+5V','BOOST_FB','battery'))
    add(R('R95','100k','BOOST_FB','GND','battery',note='0.595V reference: 4.950V nominal PWM output'))
    add(C('C93','10uF 10V','VSYS','GND','battery',c8))
    add(C('C94','22uF 10V','+5V','GND','battery',c12))
    add(C('C95','22uF 10V','+5V','GND','battery',c12))
    add(P('U16','QuadCAN:TLV3012B',s6,'TLV3012B','TI TLV3012BIDBVR',
          {'1':'BOOST_EN','2':'GND','3':'UVLO_SENSE','4':'UVLO_REF','5':'UVLO_REF','6':'VSYS'},'battery','Hardware hysteresis: ~3.16V off / ~3.66V restart, nominal; not pack protection'))
    add(R('R96','1M','VSYS','UVLO_SENSE','battery'))
    add(R('R97','560k','UVLO_SENSE','GND','battery'))
    add(R('R98','6.34M','BOOST_EN','UVLO_SENSE','battery'))
    add(R('R99','1M','BOOST_EN','GND','battery'))
    add(C('C96','100nF','VSYS','GND','battery'))
    add(C('C97','1nF','UVLO_REF','GND','battery'))
    # A second expander gives status inputs without consuming boot strap GPIOs.
    add(P('U17','Interface_Expansion:TCA9535PWR','Package_SO:TSSOP-24_4.4x7.8mm_P0.65mm','TCA9535 0x21','TI TCA9535PWR',
          {'2':'GND','3':'GND','21':'+3V3','22':'I2C_SCL','23':'I2C_SDA','24':'+3V3','12':'GND','4':'PGOOD_N','5':'CHG_N'},'battery','All pins input; unused inputs externally grounded'))
    for pin in ('6','7','8','9','10','11','13','14','15','16','17','18','19','20'): parts[-1]['pins'][pin]='GND'
    add(C('C98','100nF','+3V3','GND','battery'))
    add(P('U18','Analog_ADC:ADS1115IDGS','Package_SO:TSSOP-10_3x3mm_P0.5mm','ADS1115 0x48','TI ADS1115IDGSR',
          {'1':'GND','10':'I2C_SCL','9':'I2C_SDA','3':'GND','4':'BAT_ADC','5':'SYS_ADC','6':'GND','7':'GND','8':'+3V3'},'battery','AIN0 battery / AIN1 system, both divided by 4.03; ALERT unused'))
    add(C('C99','100nF','+3V3','GND','battery'))
    for top,bot,cap,rail,net in [('R100','R101','C100','BAT','BAT_ADC'),('R102','R103','C101','VSYS','SYS_ADC')]:
        add(R(top,'100k',rail,net,'battery')); add(R(bot,'33k',net,'GND','battery')); add(C(cap,'100nF',net,'GND','battery'))
    add(P('U19','74xGxx:74LVC1G08',s5,'74LVC1G08','TI SN74LVC1G08DBVR',{'1':'CAN3_INT_N','2':'CAN4_INT_N','3':'GND','4':'CAN34_INT','5':'+3V3'},'can3','Active-low interrupts combined without tying outputs together'))
    add(R('R104','10k','+3V3','CAN4_INT_N','can3'))
    add(C('C102','100nF','+3V3','GND','can3'))
    add(P('U20','74xGxx:74LVC1G125',s5,'74LVC1G125','TI SN74LVC1G125DBVR',{'1':'GPS_PWR_N','2':'GPS_TX_STRAP','3':'GND','4':'GPS_TX_BUFFERED','5':'+3V3'},'gps','OE high while GPS off; boot GPIO27 sees only buffer input'))
    add(R('R105','10k','+3V3','GPS_TX_STRAP','gps'))
    add(C('C103','100nF','+3V3','GND','gps'))

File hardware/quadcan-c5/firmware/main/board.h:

// QuadCAN-C5 board pin map - must match hardware/quadcan-c5/gen/design.py (U3 pin table)
#pragma once
#include "driver/gpio.h"

// ---- CAN channels -------------------------------------------------------
// CAN1/CAN2: ESP32-C5 on-chip CAN-FD controllers (TWAI0/TWAI1)
#define PIN_CAN1_TX        GPIO_NUM_0
#define PIN_CAN1_RX        GPIO_NUM_3    // LP GPIO -> deep-sleep wake on bus activity
#define PIN_CAN2_TX        GPIO_NUM_8
#define PIN_CAN2_RX        GPIO_NUM_1
// CAN3/CAN4: MCP2518FD on SPI2 (shared with microSD)
#define PIN_SPI_MISO       GPIO_NUM_2    // IOMUX FSPIQ
#define PIN_SPI_SCK        GPIO_NUM_6    // IOMUX FSPICLK
#define PIN_SPI_MOSI       GPIO_NUM_7    // IOMUX FSPID
#define PIN_CAN3_CS        GPIO_NUM_9
#define PIN_CAN4_CS        GPIO_NUM_10
#define PIN_MCP_INT        GPIO_NUM_23   // U19 AND of independent active-low MCP interrupts
#define PIN_SD_CS          GPIO_NUM_24

// ---- I2C: TCA9535 expander (0x20), PCF8523 RTC (0x68), Qwiic ------------
#define PIN_I2C_SDA        GPIO_NUM_25
#define PIN_I2C_SCL        GPIO_NUM_28   // also the BOOT strap / BOOT button
#define I2C_ADDR_EXPANDER  0x20
#define I2C_ADDR_POWER     0x21
#define I2C_ADDR_BAT_ADC   0x48
#define I2C_ADDR_RTC       0x68

// ---- deep-sleep wake inputs (all LP GPIOs, all active low) ----------------
// CAN1/CAN2: the transceiver in standby pulls RXD low on bus activity (PIN_CAN1_RX / PIN_CAN2_RX).
// WAKE_N:    diode-OR of CAN3_RXD, CAN4_RXD and the ignition input.
#define PIN_WAKE_N         GPIO_NUM_5
#define WAKE_PIN_MASK      ((1ULL << PIN_CAN1_RX) | (1ULL << PIN_CAN2_RX) | (1ULL << PIN_WAKE_N))

// ---- analog --------------------------------------------------------------
#define PIN_VIN_SENSE      GPIO_NUM_4    // ADC1_CH3, VIN / 11
#define VIN_DIVIDER        11.0f
#define VIN_DIODE_DROP_V   0.45f         // D2 reverse-polarity diode sits before the divider

// ---- UARTs ---------------------------------------------------------------
#define PIN_GPS_TX         GPIO_NUM_27   // boot strap -> U20 -> NEO-M9N RXD
#define PIN_GPS_RX         GPIO_NUM_26   // NEO-M9N TXD -> ESP
#define PIN_LTE_TX         GPIO_NUM_11   // U0TXD -> LTE module RXD
#define PIN_LTE_RX         GPIO_NUM_12   // U0RXD <- LTE module TXD

// ---- TCA9535 expander bit numbers (port0 = 0..7, port1 = 8..15) ---------
enum {
    XP_CAN1_STB = 0, XP_CAN2_STB, XP_LED_STAT_N, XP_LED_SD_N, XP_LED_LINK_N, XP_OSC_EN,
    XP_GPS_PWR_N, XP_LTE_PWRKEY,
    XP_IGN_N = 8, XP_CABLE_ID0, XP_CABLE_ID1, XP_SD_DET, XP_GPS_RESET_N, XP_LTE_STATUS,
    XP_BTN_MARK_N, XP_SD_PWR_N,
};
// Pins the firmware drives. Everything else stays an input, which is also the reset state:
// STB lines float high (transceivers in standby), GPS and SD card power off, oscillator enabled.
#define XP_OUTPUT_MASK  ((1u << XP_CAN1_STB) | (1u << XP_CAN2_STB) | (1u << XP_LED_STAT_N) | \
                         (1u << XP_LED_SD_N) | (1u << XP_LED_LINK_N) | (1u << XP_OSC_EN) |   \
                         (1u << XP_GPS_PWR_N) | (1u << XP_LTE_PWRKEY) | (1u << XP_SD_PWR_N))

// Cable identification (cable grounds ID0/ID1; open = 1)
typedef enum {
    CABLE_NONE = 3,        // ID1=1 ID0=1 : nothing / bench
    CABLE_OBD2 = 2,        // ID1=1 ID0=0 : OBD-II (CAN1 = pins 6/14)
    CABLE_J1939 = 1,       // ID1=0 ID0=1 : Deutsch 9-pin (CAN1 = C/D, CAN2 = H/J)
    CABLE_CUSTOM = 0,      // both grounded: user cable, config from SD
} cable_id_t;

#define NUM_CAN 4

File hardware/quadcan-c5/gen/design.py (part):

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      "WAKE_N goes low on CAN3/CAN4 bus activity (transceiver in standby) or ignition on"))
add(P("D41", "Diode:BAT54A", SOT23, "BAT54A", "BAT54A dual Schottky, common anode",
      {"1": "IGN_N", "2": "IGN_N", "3": "WAKE_N"}, "sense"))
add(R("R67", "100k", "+3V3", "WAKE_N", "sense", note="Deep-sleep wake sources: GPIO3 CAN1_RXD, GPIO1 CAN2_RXD, GPIO5 WAKE_N"))
add(R("R13", "1k", "CABLE_ID0_RAW", "CABLE_ID0", "sense"))
add(R("R14", "1M", "+3V3", "CABLE_ID0", "sense"))
add(R("R15", "1k", "CABLE_ID1_RAW", "CABLE_ID1", "sense"))
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add(P("SW1", "Switch:SW_Push", "Button_Switch_SMD:SW_SPST_PTS810", "RESET", "C&K PTS810 SJM 250 SMTR LFS",
      {"1": "EN", "2": "GND"}, "mcu"))
add(P("SW2", "Switch:SW_Push", "Button_Switch_SMD:SW_SPST_PTS810", "BOOT", "C&K PTS810 SJM 250 SMTR LFS",
      {"1": "I2C_SCL", "2": "GND"}, "mcu", "Hold BOOT while tapping RESET for download mode"))
add(R("R18", "4.7k", "+3V3", "I2C_SDA", "mcu"))
add(R("R19", "4.7k", "+3V3", "I2C_SCL", "mcu"))
add(R("R20", "10k", "SD_3V3", "SD_CS", "mcu"))
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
